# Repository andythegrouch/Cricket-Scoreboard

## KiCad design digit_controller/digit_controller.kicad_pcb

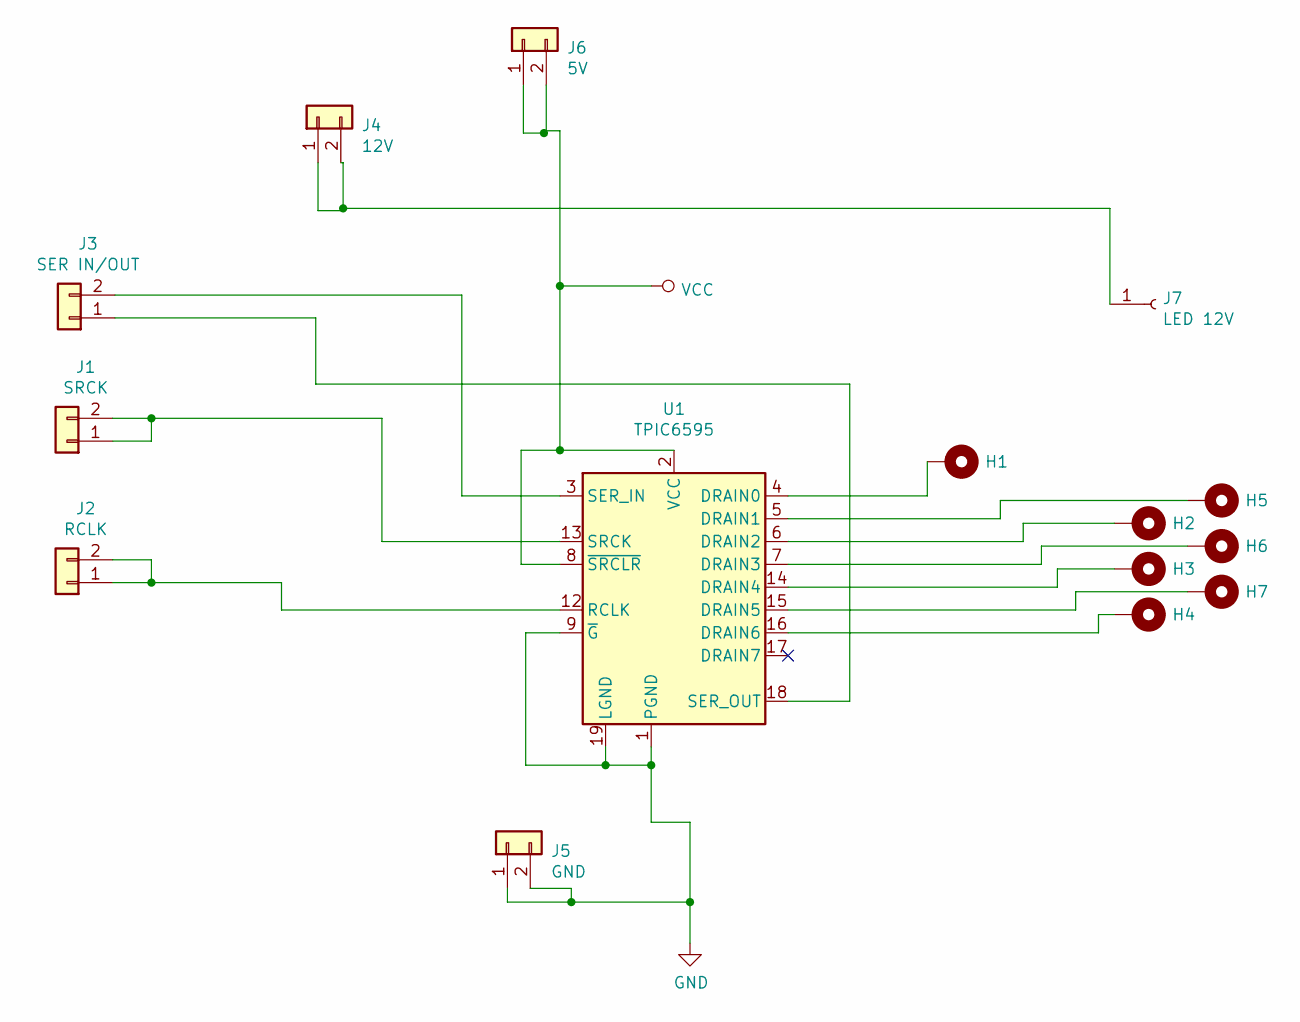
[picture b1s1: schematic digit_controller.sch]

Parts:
H1, H2, H3, H4, H5, H6, H7: MountingHole_Pad; Pin_D1.0mm_L10.0mm_LooseFit
J1: SRCK; TerminalBlock_Altech_AK300-2_P5.00mm
J2: RCLK; TerminalBlock_Altech_AK300-2_P5.00mm
J3: SER IN/OUT; TerminalBlock_Altech_AK300-2_P5.00mm
J4: 12V; TerminalBlock_Altech_AK300-2_P5.00mm
J5: GND; TerminalBlock_Altech_AK300-2_P5.00mm
J6: 5V; TerminalBlock_Altech_AK300-2_P5.00mm
J7: LED 12V; Pin_D1.3mm_L11.0mm
U1: TPIC6595; DIP-20_W7.62mm_Socket_LongPads

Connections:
GND: J5.1, J5.2, U1.1 (PGND), U1.9 (~G), U1.10 (PGND), U1.11 (PGND), U1.19 (LGND), U1.20 (PGND)
unnamed: H1.1, U1.4 (DRAIN0)
unnamed: H2.1, U1.6 (DRAIN2)
unnamed: H3.1, U1.14 (DRAIN4)
unnamed: H4.1, U1.16 (DRAIN6)
unnamed: H5.1, U1.5 (DRAIN1)
unnamed: H6.1, U1.7 (DRAIN3)
unnamed: H7.1, U1.15 (DRAIN5)
unnamed: J1.1, J1.2, U1.13 (SRCK)
unnamed: J2.1, J2.2, U1.12 (RCLK)
unnamed: J3.1, U1.18 (SER_OUT)
unnamed: J3.2, U1.3 (SER_IN)
unnamed: J4.1, J4.2, J7.1
VCC: J6.1, J6.2, U1.2 (VCC), U1.8 (~SRCLR)

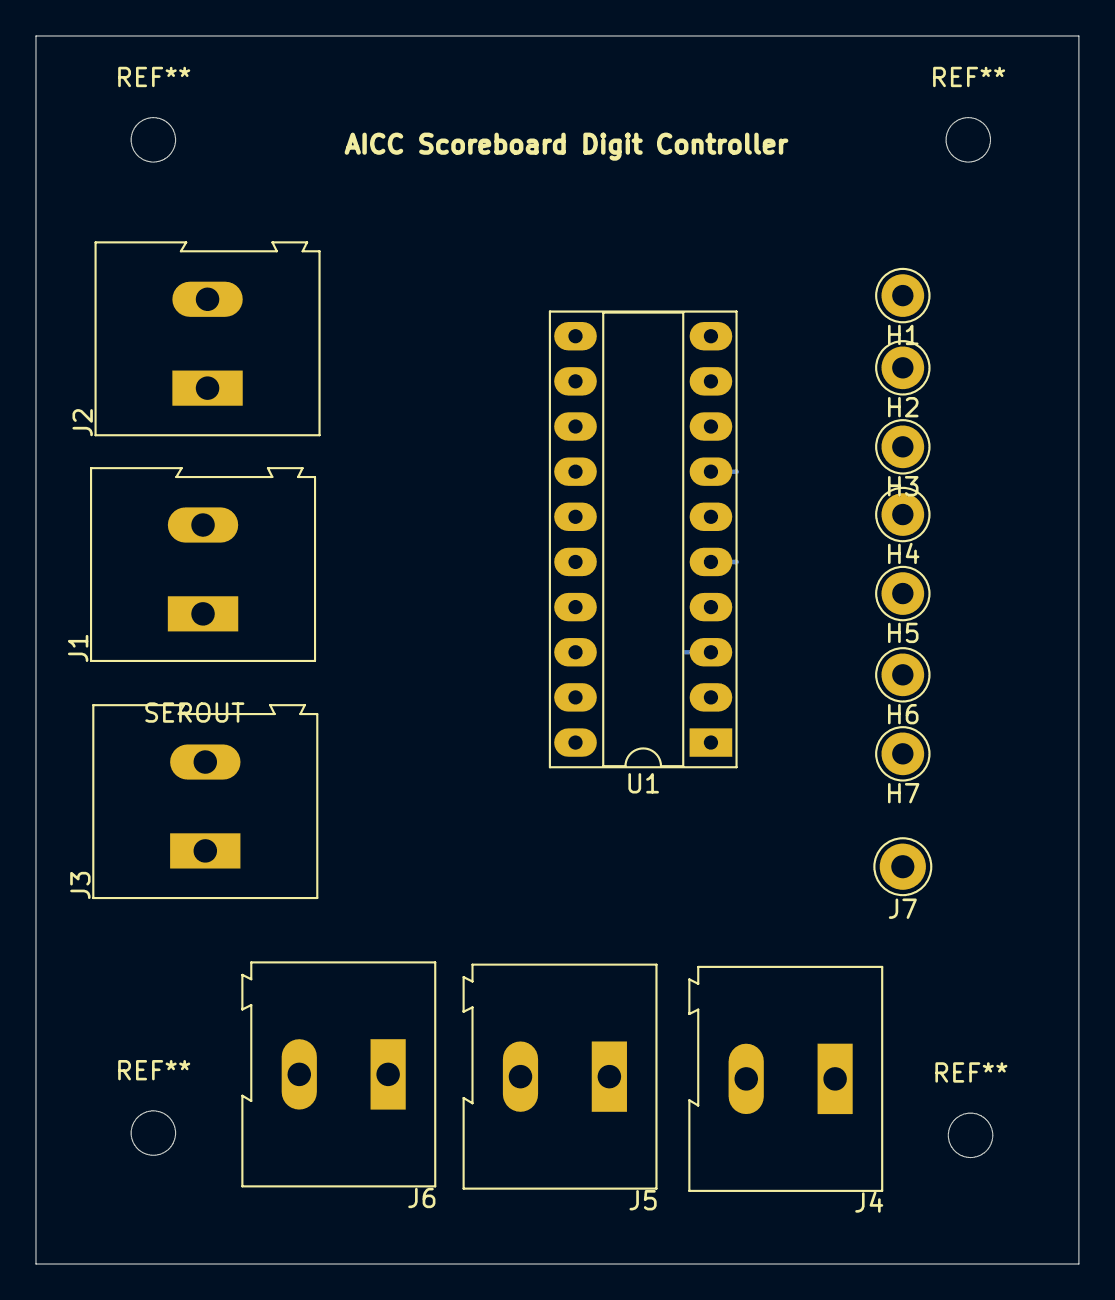
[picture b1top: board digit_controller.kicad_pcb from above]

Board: 2 copper layers, 58.7 x 69.1 mm, 15 parts (0 on the bottom side), 14 nets.
